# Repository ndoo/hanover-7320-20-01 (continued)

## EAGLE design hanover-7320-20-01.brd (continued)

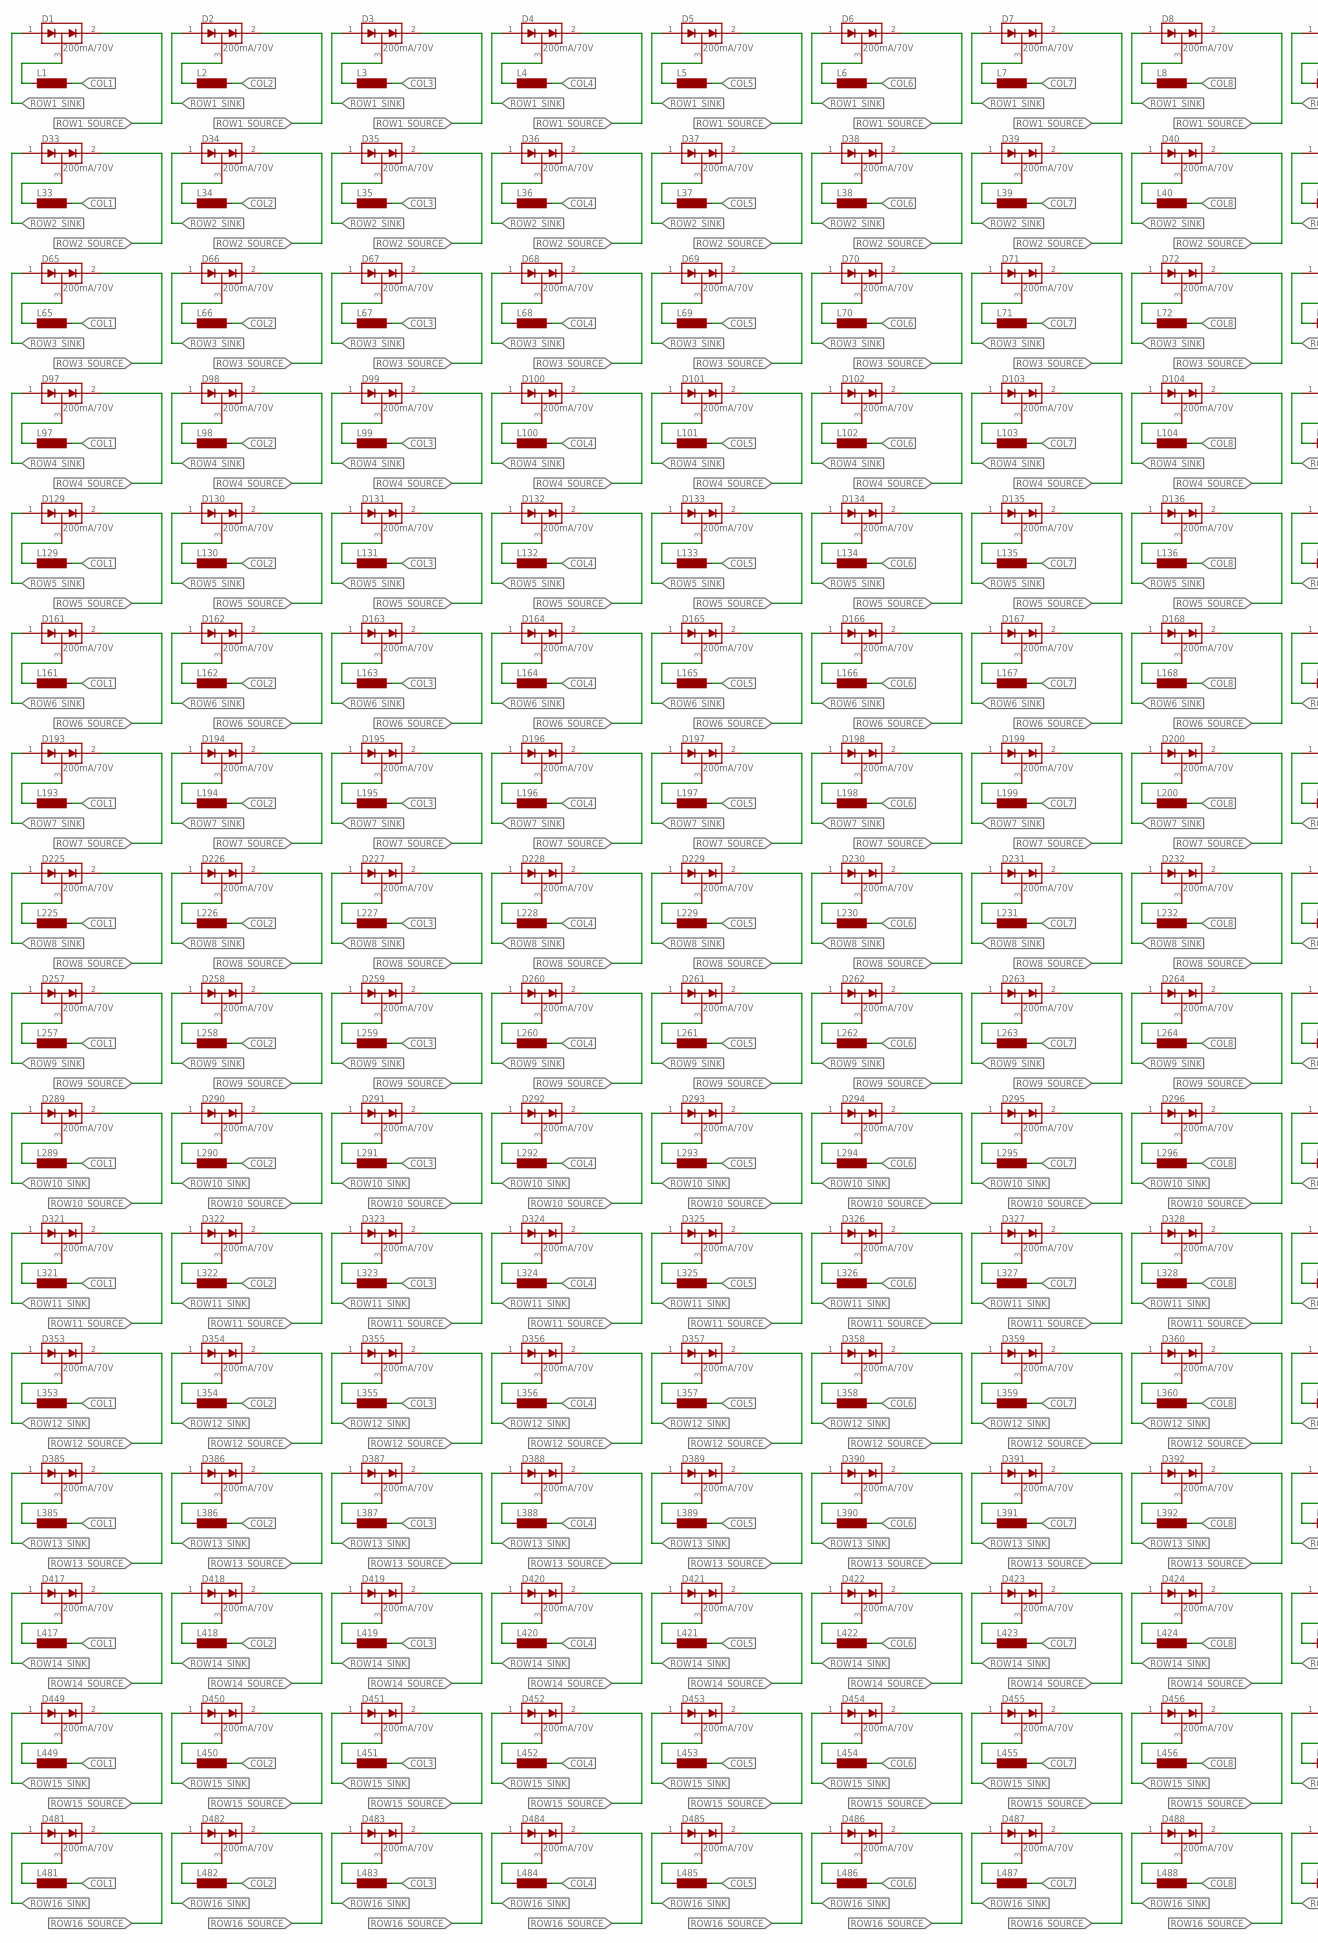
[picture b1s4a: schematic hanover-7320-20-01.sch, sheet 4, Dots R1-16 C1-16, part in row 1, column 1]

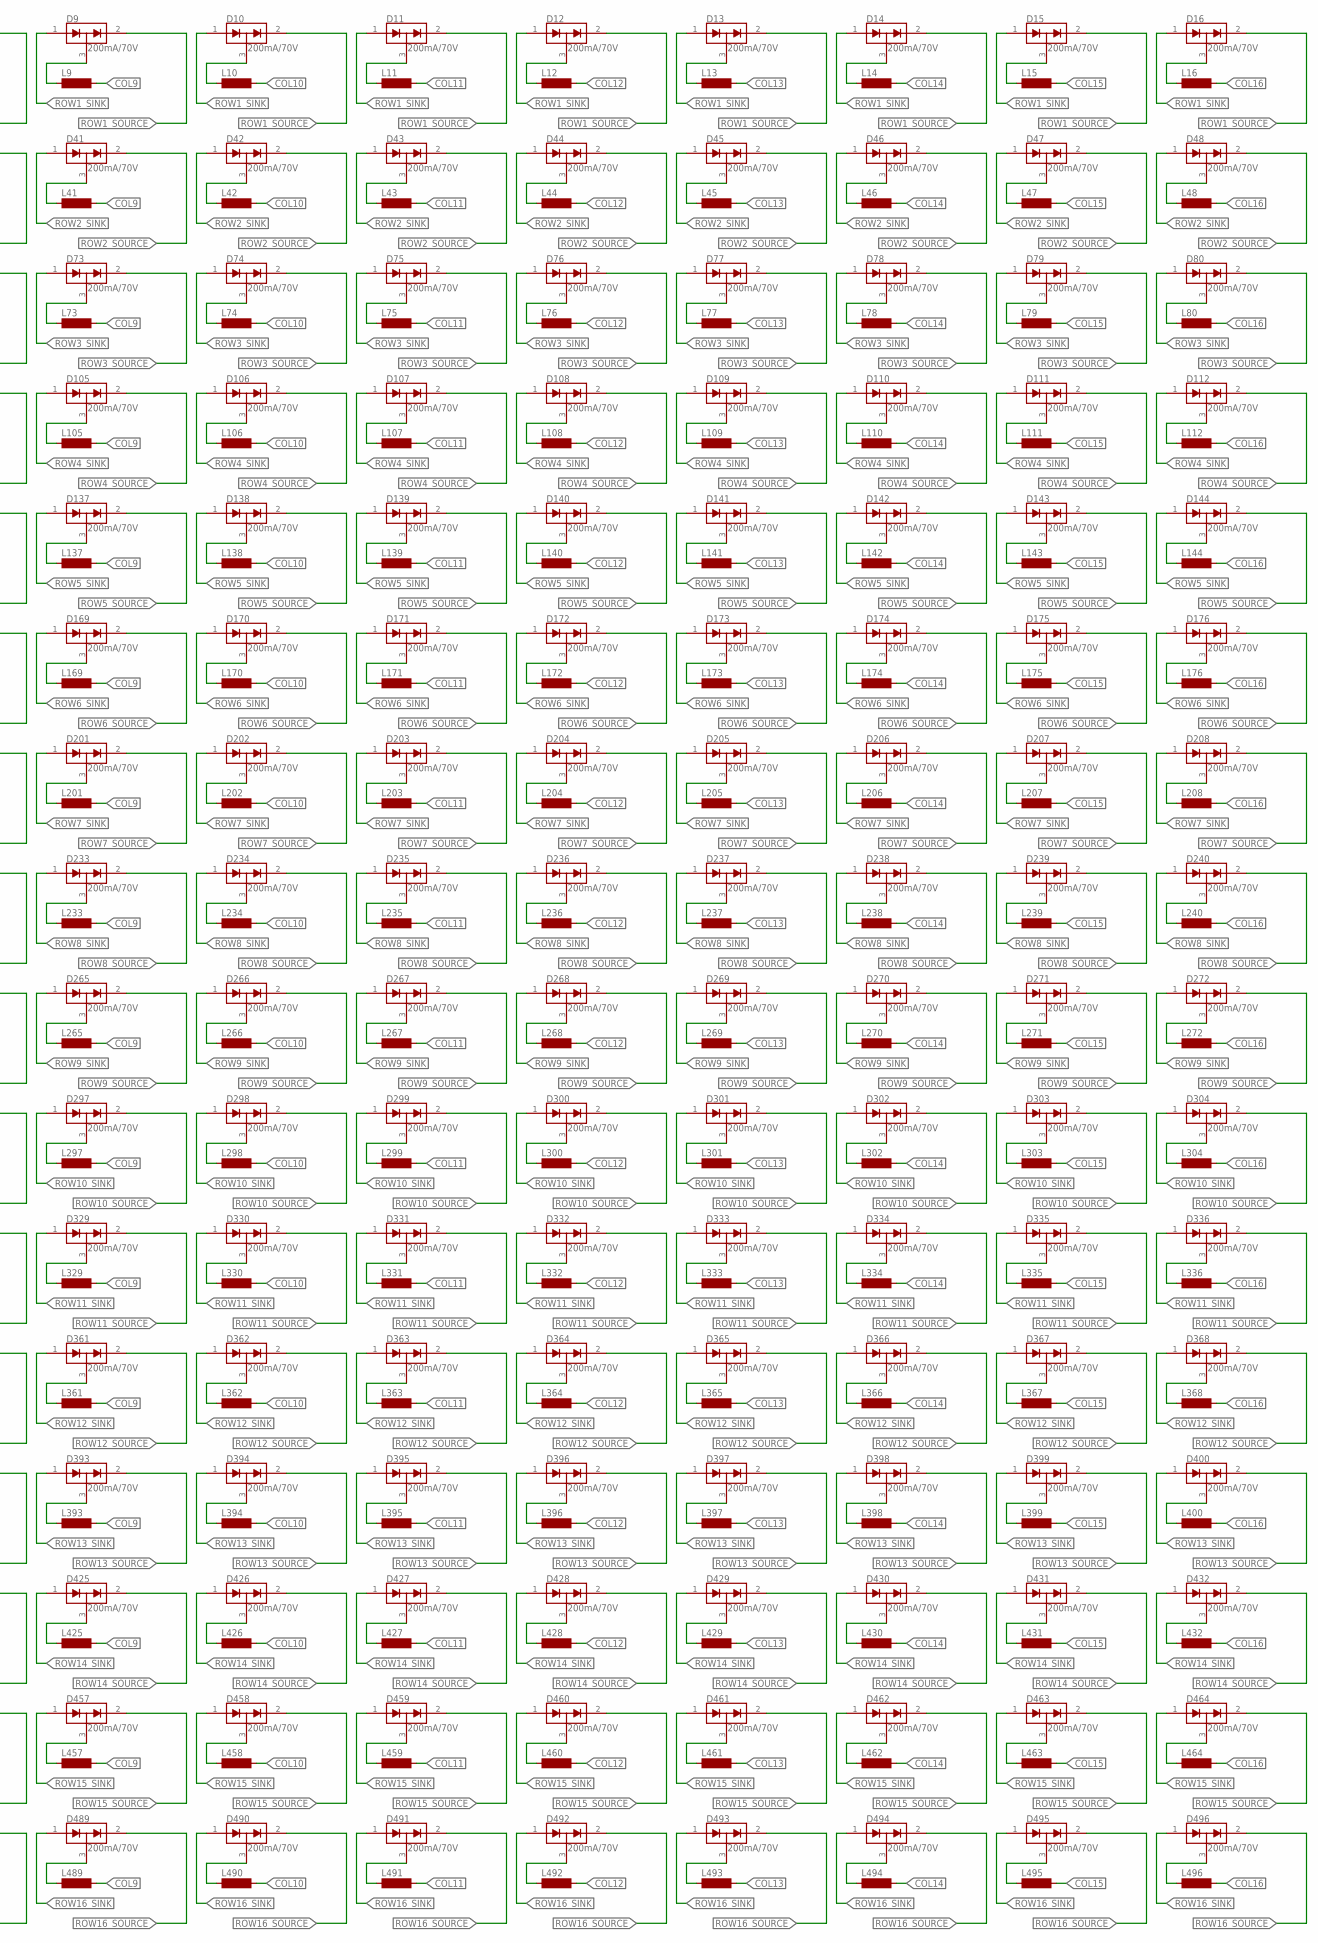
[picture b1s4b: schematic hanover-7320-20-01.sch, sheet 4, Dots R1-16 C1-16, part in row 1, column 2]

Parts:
D1, D2, D3, D4, D5, D6, D7, D8, D9, D10, D11, D12, D13, D14, D15, D16, D33, D34, D35, D36, D37, D38, D39, D40, D41, D42, D43, D44, D45, D46, D47, D48, D65, D66, D67, D68, D69, D70, D71, D72, D73, D74, D75, D76, D77, D78, D79, D80, D97, D98, D99, D100, D101, D102, D103, D104, D105, D106, D107, D108, D109, D110, D111, D112, D129, D130, D131, D132, D133, D134, D135, D136, D137, D138, D139, D140, D141, D142, D143, D144, D161, D162, D163, D164, D165, D166, D167, D168, D169, D170, D171, D172, D173, D174, D175, D176, D193, D194, D195, D196, D197, D198, D199, D200, D201, D202, D203, D204, D205, D206, D207, D208, D225, D226, D227, D228, D229, D230, D231, D232, D233, D234, D235, D236, D237, D238, D239, D240, D257, D258, D259, D260, D261, D262, D263, D264, D265, D266, D267, D268, D269, D270, D271, D272, D289, D290, D291, D292, D293, D294, D295, D296, D297, D298, D299, D300, D301, D302, D303, D304, D321, D322, D323, D324, D325, D326, D327, D328, D329, D330, D331, D332, D333, D334, D335, D336, D353, D354, D355, D356, D357, D358, D359, D360, D361, D362, D363, D364, D365, D366, D367, D368, D385, D386, D387, D388, D389, D390, D391, D392, D393, D394, D395, D396, D397, D398, D399, D400, D417, D418, D419, D420, D421, D422, D423, D424, D425, D426, D427, D428, D429, D430, D431, D432, D449, D450, D451, D452, D453, D454, D455, D456, D457, D458, D459, D460, D461, D462, D463, D464, D481, D482, D483, D484, D485, D486, D487, D488, D489, D490, D491, D492, D493, D494, D495, D496: 200mA/70V; SOT23-3
L1, L2, L3, L4, L5, L6, L7, L8, L9, L10, L11, L12, L13, L14, L15, L16, L33, L34, L35, L36, L37, L38, L39, L40, L41, L42, L43, L44, L45, L46, L47, L48, L65, L66, L67, L68, L69, L70, L71, L72, L73, L74, L75, L76, L77, L78, L79, L80, L97, L98, L99, L100, L101, L102, L103, L104, L105, L106, L107, L108, L109, L110, L111, L112, L129, L130, L131, L132, L133, L134, L135, L136, L137, L138, L139, L140, L141, L142, L143, L144, L161, L162, L163, L164, L165, L166, L167, L168, L169, L170, L171, L172, L173, L174, L175, L176, L193, L194, L195, L196, L197, L198, L199, L200, L201, L202, L203, L204, L205, L206, L207, L208, L225, L226, L227, L228, L229, L230, L231, L232, L233, L234, L235, L236, L237, L238, L239, L240, L257, L258, L259, L260, L261, L262, L263, L264, L265, L266, L267, L268, L269, L270, L271, L272, L289, L290, L291, L292, L293, L294, L295, L296, L297, L298, L299, L300, L301, L302, L303, L304, L321, L322, L323, L324, L325, L326, L327, L328, L329, L330, L331, L332, L333, L334, L335, L336, L353, L354, L355, L356, L357, L358, L359, L360, L361, L362, L363, L364, L365, L366, L367, L368, L385, L386, L387, L388, L389, L390, L391, L392, L393, L394, L395, L396, L397, L398, L399, L400, L417, L418, L419, L420, L421, L422, L423, L424, L425, L426, L427, L428, L429, L430, L431, L432, L449, L450, L451, L452, L453, L454, L455, L456, L457, L458, L459, L460, L461, L462, L463, L464, L481, L482, L483, L484, L485, L486, L487, L488, L489, L490, L491, L492, L493, L494, L495, L496: SD8

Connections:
COL1: L1.2, L33.2, L65.2, L97.2, L129.2, L161.2, L193.2, L225.2, L257.2, L289.2, L321.2, L353.2, L385.2, L417.2, L449.2, L481.2; also elsewhere on the board
COL2: L2.2, L34.2, L66.2, L98.2, L130.2, L162.2, L194.2, L226.2, L258.2, L290.2, L322.2, L354.2, L386.2, L418.2, L450.2, L482.2; also elsewhere on the board
COL3: L3.2, L35.2, L67.2, L99.2, L131.2, L163.2, L195.2, L227.2, L259.2, L291.2, L323.2, L355.2, L387.2, L419.2, L451.2, L483.2; also elsewhere on the board
COL4: L4.2, L36.2, L68.2, L100.2, L132.2, L164.2, L196.2, L228.2, L260.2, L292.2, L324.2, L356.2, L388.2, L420.2, L452.2, L484.2; also elsewhere on the board
COL5: L5.2, L37.2, L69.2, L101.2, L133.2, L165.2, L197.2, L229.2, L261.2, L293.2, L325.2, L357.2, L389.2, L421.2, L453.2, L485.2; also elsewhere on the board
COL6: L6.2, L38.2, L70.2, L102.2, L134.2, L166.2, L198.2, L230.2, L262.2, L294.2, L326.2, L358.2, L390.2, L422.2, L454.2, L486.2; also elsewhere on the board
COL7: L7.2, L39.2, L71.2, L103.2, L135.2, L167.2, L199.2, L231.2, L263.2, L295.2, L327.2, L359.2, L391.2, L423.2, L455.2, L487.2; also elsewhere on the board
COL8: L8.2, L40.2, L72.2, L104.2, L136.2, L168.2, L200.2, L232.2, L264.2, L296.2, L328.2, L360.2, L392.2, L424.2, L456.2, L488.2; also elsewhere on the board
COL9: L9.2, L41.2, L73.2, L105.2, L137.2, L169.2, L201.2, L233.2, L265.2, L297.2, L329.2, L361.2, L393.2, L425.2, L457.2, L489.2; also elsewhere on the board
COL10: L10.2, L42.2, L74.2, L106.2, L138.2, L170.2, L202.2, L234.2, L266.2, L298.2, L330.2, L362.2, L394.2, L426.2, L458.2, L490.2; also elsewhere on the board
COL11: L11.2, L43.2, L75.2, L107.2, L139.2, L171.2, L203.2, L235.2, L267.2, L299.2, L331.2, L363.2, L395.2, L427.2, L459.2, L491.2; also elsewhere on the board
COL12: L12.2, L44.2, L76.2, L108.2, L140.2, L172.2, L204.2, L236.2, L268.2, L300.2, L332.2, L364.2, L396.2, L428.2, L460.2, L492.2; also elsewhere on the board
COL13: L13.2, L45.2, L77.2, L109.2, L141.2, L173.2, L205.2, L237.2, L269.2, L301.2, L333.2, L365.2, L397.2, L429.2, L461.2, L493.2; also elsewhere on the board
COL14: L14.2, L46.2, L78.2, L110.2, L142.2, L174.2, L206.2, L238.2, L270.2, L302.2, L334.2, L366.2, L398.2, L430.2, L462.2, L494.2; also elsewhere on the board
COL15: L15.2, L47.2, L79.2, L111.2, L143.2, L175.2, L207.2, L239.2, L271.2, L303.2, L335.2, L367.2, L399.2, L431.2, L463.2, L495.2; also elsewhere on the board
COL16: L16.2, L48.2, L80.2, L112.2, L144.2, L176.2, L208.2, L240.2, L272.2, L304.2, L336.2, L368.2, L400.2, L432.2, L464.2, L496.2; also elsewhere on the board
unnamed: D1.3 (COM), L1.1
unnamed: D2.3 (COM), L2.1
unnamed: D3.3 (COM), L3.1
unnamed: D4.3 (COM), L4.1
unnamed: D5.3 (COM), L5.1
unnamed: D6.3 (COM), L6.1
unnamed: D7.3 (COM), L7.1
unnamed: D8.3 (COM), L8.1
unnamed: D9.3 (COM), L9.1
unnamed: D10.3 (COM), L10.1
unnamed: D11.3 (COM), L11.1
unnamed: D12.3 (COM), L12.1
unnamed: D13.3 (COM), L13.1
unnamed: D14.3 (COM), L14.1
unnamed: D15.3 (COM), L15.1
unnamed: D16.3 (COM), L16.1
unnamed: D33.3 (COM), L33.1
unnamed: D34.3 (COM), L34.1
unnamed: D35.3 (COM), L35.1
unnamed: D36.3 (COM), L36.1
unnamed: D37.3 (COM), L37.1
unnamed: D38.3 (COM), L38.1
unnamed: D39.3 (COM), L39.1
unnamed: D40.3 (COM), L40.1
unnamed: D41.3 (COM), L41.1
unnamed: D42.3 (COM), L42.1
unnamed: D43.3 (COM), L43.1
unnamed: D44.3 (COM), L44.1
unnamed: D45.3 (COM), L45.1
unnamed: D46.3 (COM), L46.1
unnamed: D47.3 (COM), L47.1
unnamed: D48.3 (COM), L48.1
unnamed: D65.3 (COM), L65.1
unnamed: D66.3 (COM), L66.1
unnamed: D67.3 (COM), L67.1
unnamed: D68.3 (COM), L68.1
unnamed: D69.3 (COM), L69.1
unnamed: D70.3 (COM), L70.1
unnamed: D71.3 (COM), L71.1
unnamed: D72.3 (COM), L72.1
unnamed: D73.3 (COM), L73.1
unnamed: D74.3 (COM), L74.1
unnamed: D75.3 (COM), L75.1
unnamed: D76.3 (COM), L76.1
unnamed: D77.3 (COM), L77.1
unnamed: D78.3 (COM), L78.1
unnamed: D79.3 (COM), L79.1
unnamed: D80.3 (COM), L80.1
unnamed: D97.3 (COM), L97.1
unnamed: D98.3 (COM), L98.1
unnamed: D99.3 (COM), L99.1
unnamed: D100.3 (COM), L100.1
unnamed: D101.3 (COM), L101.1
unnamed: D102.3 (COM), L102.1
unnamed: D103.3 (COM), L103.1
unnamed: D104.3 (COM), L104.1
unnamed: D105.3 (COM), L105.1
unnamed: D106.3 (COM), L106.1
unnamed: D107.3 (COM), L107.1
unnamed: D108.3 (COM), L108.1
unnamed: D109.3 (COM), L109.1
unnamed: D110.3 (COM), L110.1
unnamed: D111.3 (COM), L111.1
unnamed: D112.3 (COM), L112.1
unnamed: D129.3 (COM), L129.1
unnamed: D130.3 (COM), L130.1
unnamed: D131.3 (COM), L131.1
unnamed: D132.3 (COM), L132.1
unnamed: D133.3 (COM), L133.1
unnamed: D134.3 (COM), L134.1
unnamed: D135.3 (COM), L135.1
unnamed: D136.3 (COM), L136.1
unnamed: D137.3 (COM), L137.1
unnamed: D138.3 (COM), L138.1
unnamed: D139.3 (COM), L139.1
unnamed: D140.3 (COM), L140.1
unnamed: D141.3 (COM), L141.1
unnamed: D142.3 (COM), L142.1
unnamed: D143.3 (COM), L143.1
unnamed: D144.3 (COM), L144.1
unnamed: D161.3 (COM), L161.1
unnamed: D162.3 (COM), L162.1
unnamed: D163.3 (COM), L163.1
unnamed: D164.3 (COM), L164.1
unnamed: D165.3 (COM), L165.1
unnamed: D166.3 (COM), L166.1
unnamed: D167.3 (COM), L167.1
unnamed: D168.3 (COM), L168.1
unnamed: D169.3 (COM), L169.1
unnamed: D170.3 (COM), L170.1
unnamed: D171.3 (COM), L171.1
unnamed: D172.3 (COM), L172.1
unnamed: D173.3 (COM), L173.1
unnamed: D174.3 (COM), L174.1
unnamed: D175.3 (COM), L175.1
unnamed: D176.3 (COM), L176.1
unnamed: D193.3 (COM), L193.1
unnamed: D194.3 (COM), L194.1
unnamed: D195.3 (COM), L195.1
unnamed: D196.3 (COM), L196.1
unnamed: D197.3 (COM), L197.1
unnamed: D198.3 (COM), L198.1
unnamed: D199.3 (COM), L199.1
unnamed: D200.3 (COM), L200.1
unnamed: D201.3 (COM), L201.1
unnamed: D202.3 (COM), L202.1
unnamed: D203.3 (COM), L203.1
unnamed: D204.3 (COM), L204.1
unnamed: D205.3 (COM), L205.1
unnamed: D206.3 (COM), L206.1
unnamed: D207.3 (COM), L207.1
unnamed: D208.3 (COM), L208.1
unnamed: D225.3 (COM), L225.1
unnamed: D226.3 (COM), L226.1
unnamed: D227.3 (COM), L227.1
unnamed: D228.3 (COM), L228.1
unnamed: D229.3 (COM), L229.1
unnamed: D230.3 (COM), L230.1
unnamed: D231.3 (COM), L231.1
unnamed: D232.3 (COM), L232.1
unnamed: D233.3 (COM), L233.1
unnamed: D234.3 (COM), L234.1
unnamed: D235.3 (COM), L235.1
unnamed: D236.3 (COM), L236.1
unnamed: D237.3 (COM), L237.1
unnamed: D238.3 (COM), L238.1
unnamed: D239.3 (COM), L239.1
unnamed: D240.3 (COM), L240.1
unnamed: D257.3 (COM), L257.1
unnamed: D258.3 (COM), L258.1
unnamed: D259.3 (COM), L259.1
unnamed: D260.3 (COM), L260.1
unnamed: D261.3 (COM), L261.1
unnamed: D262.3 (COM), L262.1
unnamed: D263.3 (COM), L263.1
unnamed: D264.3 (COM), L264.1
unnamed: D265.3 (COM), L265.1
unnamed: D266.3 (COM), L266.1
unnamed: D267.3 (COM), L267.1
unnamed: D268.3 (COM), L268.1
unnamed: D269.3 (COM), L269.1
unnamed: D270.3 (COM), L270.1
unnamed: D271.3 (COM), L271.1
unnamed: D272.3 (COM), L272.1
unnamed: D289.3 (COM), L289.1
unnamed: D290.3 (COM), L290.1
unnamed: D291.3 (COM), L291.1
unnamed: D292.3 (COM), L292.1
unnamed: D293.3 (COM), L293.1
unnamed: D294.3 (COM), L294.1
unnamed: D295.3 (COM), L295.1
unnamed: D296.3 (COM), L296.1
unnamed: D297.3 (COM), L297.1
unnamed: D298.3 (COM), L298.1
unnamed: D299.3 (COM), L299.1
unnamed: D300.3 (COM), L300.1
unnamed: D301.3 (COM), L301.1
unnamed: D302.3 (COM), L302.1
unnamed: D303.3 (COM), L303.1
unnamed: D304.3 (COM), L304.1
unnamed: D321.3 (COM), L321.1
unnamed: D322.3 (COM), L322.1
unnamed: D323.3 (COM), L323.1
unnamed: D324.3 (COM), L324.1
unnamed: D325.3 (COM), L325.1
unnamed: D326.3 (COM), L326.1
unnamed: D327.3 (COM), L327.1
unnamed: D328.3 (COM), L328.1
unnamed: D329.3 (COM), L329.1
unnamed: D330.3 (COM), L330.1
unnamed: D331.3 (COM), L331.1
unnamed: D332.3 (COM), L332.1
unnamed: D333.3 (COM), L333.1
unnamed: D334.3 (COM), L334.1
unnamed: D335.3 (COM), L335.1
unnamed: D336.3 (COM), L336.1
unnamed: D353.3 (COM), L353.1
unnamed: D354.3 (COM), L354.1
unnamed: D355.3 (COM), L355.1
unnamed: D356.3 (COM), L356.1
unnamed: D357.3 (COM), L357.1
unnamed: D358.3 (COM), L358.1
unnamed: D359.3 (COM), L359.1
unnamed: D360.3 (COM), L360.1
unnamed: D361.3 (COM), L361.1
unnamed: D362.3 (COM), L362.1
unnamed: D363.3 (COM), L363.1
unnamed: D364.3 (COM), L364.1
unnamed: D365.3 (COM), L365.1
unnamed: D366.3 (COM), L366.1
unnamed: D367.3 (COM), L367.1
unnamed: D368.3 (COM), L368.1
unnamed: D385.3 (COM), L385.1
unnamed: D386.3 (COM), L386.1
unnamed: D387.3 (COM), L387.1
unnamed: D388.3 (COM), L388.1
unnamed: D389.3 (COM), L389.1
unnamed: D390.3 (COM), L390.1
unnamed: D391.3 (COM), L391.1
unnamed: D392.3 (COM), L392.1
unnamed: D393.3 (COM), L393.1
unnamed: D394.3 (COM), L394.1
unnamed: D395.3 (COM), L395.1
unnamed: D396.3 (COM), L396.1
unnamed: D397.3 (COM), L397.1
unnamed: D398.3 (COM), L398.1
unnamed: D399.3 (COM), L399.1
unnamed: D400.3 (COM), L400.1
unnamed: D417.3 (COM), L417.1
unnamed: D418.3 (COM), L418.1
unnamed: D419.3 (COM), L419.1
unnamed: D420.3 (COM), L420.1
unnamed: D421.3 (COM), L421.1
unnamed: D422.3 (COM), L422.1
unnamed: D423.3 (COM), L423.1
unnamed: D424.3 (COM), L424.1
unnamed: D425.3 (COM), L425.1
unnamed: D426.3 (COM), L426.1
unnamed: D427.3 (COM), L427.1
unnamed: D428.3 (COM), L428.1
unnamed: D429.3 (COM), L429.1
unnamed: D430.3 (COM), L430.1
unnamed: D431.3 (COM), L431.1
unnamed: D432.3 (COM), L432.1
unnamed: D449.3 (COM), L449.1
unnamed: D450.3 (COM), L450.1
unnamed: D451.3 (COM), L451.1
unnamed: D452.3 (COM), L452.1
unnamed: D453.3 (COM), L453.1
unnamed: D454.3 (COM), L454.1
unnamed: D455.3 (COM), L455.1
unnamed: D456.3 (COM), L456.1
unnamed: D457.3 (COM), L457.1
unnamed: D458.3 (COM), L458.1
unnamed: D459.3 (COM), L459.1
unnamed: D460.3 (COM), L460.1
unnamed: D461.3 (COM), L461.1
unnamed: D462.3 (COM), L462.1
unnamed: D463.3 (COM), L463.1
unnamed: D464.3 (COM), L464.1
unnamed: D481.3 (COM), L481.1
unnamed: D482.3 (COM), L482.1
unnamed: D483.3 (COM), L483.1
unnamed: D484.3 (COM), L484.1
unnamed: D485.3 (COM), L485.1
unnamed: D486.3 (COM), L486.1
unnamed: D487.3 (COM), L487.1
unnamed: D488.3 (COM), L488.1
unnamed: D489.3 (COM), L489.1
unnamed: D490.3 (COM), L490.1
unnamed: D491.3 (COM), L491.1
unnamed: D492.3 (COM), L492.1
unnamed: D493.3 (COM), L493.1
unnamed: D494.3 (COM), L494.1
unnamed: D495.3 (COM), L495.1
unnamed: D496.3 (COM), L496.1
ROW1_SINK: D1.1 (A1), D2.1 (A1), D3.1 (A1), D4.1 (A1), D5.1 (A1), D6.1 (A1), D7.1 (A1), D8.1 (A1), D9.1 (A1), D10.1 (A1), D11.1 (A1), D12.1 (A1), D13.1 (A1), D14.1 (A1), D15.1 (A1), D16.1 (A1); also elsewhere on the board
ROW1_SOURCE: D1.2 (C2), D2.2 (C2), D3.2 (C2), D4.2 (C2), D5.2 (C2), D6.2 (C2), D7.2 (C2), D8.2 (C2), D9.2 (C2), D10.2 (C2), D11.2 (C2), D12.2 (C2), D13.2 (C2), D14.2 (C2), D15.2 (C2), D16.2 (C2); also elsewhere on the board
ROW2_SINK: D33.1 (A1), D34.1 (A1), D35.1 (A1), D36.1 (A1), D37.1 (A1), D38.1 (A1), D39.1 (A1), D40.1 (A1), D41.1 (A1), D42.1 (A1), D43.1 (A1), D44.1 (A1), D45.1 (A1), D46.1 (A1), D47.1 (A1), D48.1 (A1); also elsewhere on the board
ROW2_SOURCE: D33.2 (C2), D34.2 (C2), D35.2 (C2), D36.2 (C2), D37.2 (C2), D38.2 (C2), D39.2 (C2), D40.2 (C2), D41.2 (C2), D42.2 (C2), D43.2 (C2), D44.2 (C2), D45.2 (C2), D46.2 (C2), D47.2 (C2), D48.2 (C2); also elsewhere on the board
ROW3_SINK: D65.1 (A1), D66.1 (A1), D67.1 (A1), D68.1 (A1), D69.1 (A1), D70.1 (A1), D71.1 (A1), D72.1 (A1), D73.1 (A1), D74.1 (A1), D75.1 (A1), D76.1 (A1), D77.1 (A1), D78.1 (A1), D79.1 (A1), D80.1 (A1); also elsewhere on the board
ROW3_SOURCE: D65.2 (C2), D66.2 (C2), D67.2 (C2), D68.2 (C2), D69.2 (C2), D70.2 (C2), D71.2 (C2), D72.2 (C2), D73.2 (C2), D74.2 (C2), D75.2 (C2), D76.2 (C2), D77.2 (C2), D78.2 (C2), D79.2 (C2), D80.2 (C2); also elsewhere on the board
ROW4_SINK: D97.1 (A1), D98.1 (A1), D99.1 (A1), D100.1 (A1), D101.1 (A1), D102.1 (A1), D103.1 (A1), D104.1 (A1), D105.1 (A1), D106.1 (A1), D107.1 (A1), D108.1 (A1), D109.1 (A1), D110.1 (A1), D111.1 (A1), D112.1 (A1); also elsewhere on the board
ROW4_SOURCE: D97.2 (C2), D98.2 (C2), D99.2 (C2), D100.2 (C2), D101.2 (C2), D102.2 (C2), D103.2 (C2), D104.2 (C2), D105.2 (C2), D106.2 (C2), D107.2 (C2), D108.2 (C2), D109.2 (C2), D110.2 (C2), D111.2 (C2), D112.2 (C2); also elsewhere on the board
ROW5_SINK: D129.1 (A1), D130.1 (A1), D131.1 (A1), D132.1 (A1), D133.1 (A1), D134.1 (A1), D135.1 (A1), D136.1 (A1), D137.1 (A1), D138.1 (A1), D139.1 (A1), D140.1 (A1), D141.1 (A1), D142.1 (A1), D143.1 (A1), D144.1 (A1); also elsewhere on the board
ROW5_SOURCE: D129.2 (C2), D130.2 (C2), D131.2 (C2), D132.2 (C2), D133.2 (C2), D134.2 (C2), D135.2 (C2), D136.2 (C2), D137.2 (C2), D138.2 (C2), D139.2 (C2), D140.2 (C2), D141.2 (C2), D142.2 (C2), D143.2 (C2), D144.2 (C2); also elsewhere on the board
ROW6_SINK: D161.1 (A1), D162.1 (A1), D163.1 (A1), D164.1 (A1), D165.1 (A1), D166.1 (A1), D167.1 (A1), D168.1 (A1), D169.1 (A1), D170.1 (A1), D171.1 (A1), D172.1 (A1), D173.1 (A1), D174.1 (A1), D175.1 (A1), D176.1 (A1); also elsewhere on the board
ROW6_SOURCE: D161.2 (C2), D162.2 (C2), D163.2 (C2), D164.2 (C2), D165.2 (C2), D166.2 (C2), D167.2 (C2), D168.2 (C2), D169.2 (C2), D170.2 (C2), D171.2 (C2), D172.2 (C2), D173.2 (C2), D174.2 (C2), D175.2 (C2), D176.2 (C2); also elsewhere on the board
ROW7_SINK: D193.1 (A1), D194.1 (A1), D195.1 (A1), D196.1 (A1), D197.1 (A1), D198.1 (A1), D199.1 (A1), D200.1 (A1), D201.1 (A1), D202.1 (A1), D203.1 (A1), D204.1 (A1), D205.1 (A1), D206.1 (A1), D207.1 (A1), D208.1 (A1); also elsewhere on the board
ROW7_SOURCE: D193.2 (C2), D194.2 (C2), D195.2 (C2), D196.2 (C2), D197.2 (C2), D198.2 (C2), D199.2 (C2), D200.2 (C2), D201.2 (C2), D202.2 (C2), D203.2 (C2), D204.2 (C2), D205.2 (C2), D206.2 (C2), D207.2 (C2), D208.2 (C2); also elsewhere on the board
ROW8_SINK: D225.1 (A1), D226.1 (A1), D227.1 (A1), D228.1 (A1), D229.1 (A1), D230.1 (A1), D231.1 (A1), D232.1 (A1), D233.1 (A1), D234.1 (A1), D235.1 (A1), D236.1 (A1), D237.1 (A1), D238.1 (A1), D239.1 (A1), D240.1 (A1); also elsewhere on the board
ROW8_SOURCE: D225.2 (C2), D226.2 (C2), D227.2 (C2), D228.2 (C2), D229.2 (C2), D230.2 (C2), D231.2 (C2), D232.2 (C2), D233.2 (C2), D234.2 (C2), D235.2 (C2), D236.2 (C2), D237.2 (C2), D238.2 (C2), D239.2 (C2), D240.2 (C2); also elsewhere on the board
ROW9_SINK: D257.1 (A1), D258.1 (A1), D259.1 (A1), D260.1 (A1), D261.1 (A1), D262.1 (A1), D263.1 (A1), D264.1 (A1), D265.1 (A1), D266.1 (A1), D267.1 (A1), D268.1 (A1), D269.1 (A1), D270.1 (A1), D271.1 (A1), D272.1 (A1); also elsewhere on the board
ROW9_SOURCE: D257.2 (C2), D258.2 (C2), D259.2 (C2), D260.2 (C2), D261.2 (C2), D262.2 (C2), D263.2 (C2), D264.2 (C2), D265.2 (C2), D266.2 (C2), D267.2 (C2), D268.2 (C2), D269.2 (C2), D270.2 (C2), D271.2 (C2), D272.2 (C2); also elsewhere on the board
ROW10_SINK: D289.1 (A1), D290.1 (A1), D291.1 (A1), D292.1 (A1), D293.1 (A1), D294.1 (A1), D295.1 (A1), D296.1 (A1), D297.1 (A1), D298.1 (A1), D299.1 (A1), D300.1 (A1), D301.1 (A1), D302.1 (A1), D303.1 (A1), D304.1 (A1); also elsewhere on the board
ROW10_SOURCE: D289.2 (C2), D290.2 (C2), D291.2 (C2), D292.2 (C2), D293.2 (C2), D294.2 (C2), D295.2 (C2), D296.2 (C2), D297.2 (C2), D298.2 (C2), D299.2 (C2), D300.2 (C2), D301.2 (C2), D302.2 (C2), D303.2 (C2), D304.2 (C2); also elsewhere on the board
ROW11_SINK: D321.1 (A1), D322.1 (A1), D323.1 (A1), D324.1 (A1), D325.1 (A1), D326.1 (A1), D327.1 (A1), D328.1 (A1), D329.1 (A1), D330.1 (A1), D331.1 (A1), D332.1 (A1), D333.1 (A1), D334.1 (A1), D335.1 (A1), D336.1 (A1); also elsewhere on the board
ROW11_SOURCE: D321.2 (C2), D322.2 (C2), D323.2 (C2), D324.2 (C2), D325.2 (C2), D326.2 (C2), D327.2 (C2), D328.2 (C2), D329.2 (C2), D330.2 (C2), D331.2 (C2), D332.2 (C2), D333.2 (C2), D334.2 (C2), D335.2 (C2), D336.2 (C2); also elsewhere on the board
ROW12_SINK: D353.1 (A1), D354.1 (A1), D355.1 (A1), D356.1 (A1), D357.1 (A1), D358.1 (A1), D359.1 (A1), D360.1 (A1), D361.1 (A1), D362.1 (A1), D363.1 (A1), D364.1 (A1), D365.1 (A1), D366.1 (A1), D367.1 (A1), D368.1 (A1); also elsewhere on the board
ROW12_SOURCE: D353.2 (C2), D354.2 (C2), D355.2 (C2), D356.2 (C2), D357.2 (C2), D358.2 (C2), D359.2 (C2), D360.2 (C2), D361.2 (C2), D362.2 (C2), D363.2 (C2), D364.2 (C2), D365.2 (C2), D366.2 (C2), D367.2 (C2), D368.2 (C2); also elsewhere on the board
ROW13_SINK: D385.1 (A1), D386.1 (A1), D387.1 (A1), D388.1 (A1), D389.1 (A1), D390.1 (A1), D391.1 (A1), D392.1 (A1), D393.1 (A1), D394.1 (A1), D395.1 (A1), D396.1 (A1), D397.1 (A1), D398.1 (A1), D399.1 (A1), D400.1 (A1); also elsewhere on the board
ROW13_SOURCE: D385.2 (C2), D386.2 (C2), D387.2 (C2), D388.2 (C2), D389.2 (C2), D390.2 (C2), D391.2 (C2), D392.2 (C2), D393.2 (C2), D394.2 (C2), D395.2 (C2), D396.2 (C2), D397.2 (C2), D398.2 (C2), D399.2 (C2), D400.2 (C2); also elsewhere on the board
ROW14_SINK: D417.1 (A1), D418.1 (A1), D419.1 (A1), D420.1 (A1), D421.1 (A1), D422.1 (A1), D423.1 (A1), D424.1 (A1), D425.1 (A1), D426.1 (A1), D427.1 (A1), D428.1 (A1), D429.1 (A1), D430.1 (A1), D431.1 (A1), D432.1 (A1); also elsewhere on the board
ROW14_SOURCE: D417.2 (C2), D418.2 (C2), D419.2 (C2), D420.2 (C2), D421.2 (C2), D422.2 (C2), D423.2 (C2), D424.2 (C2), D425.2 (C2), D426.2 (C2), D427.2 (C2), D428.2 (C2), D429.2 (C2), D430.2 (C2), D431.2 (C2), D432.2 (C2); also elsewhere on the board
ROW15_SINK: D449.1 (A1), D450.1 (A1), D451.1 (A1), D452.1 (A1), D453.1 (A1), D454.1 (A1), D455.1 (A1), D456.1 (A1), D457.1 (A1), D458.1 (A1), D459.1 (A1), D460.1 (A1), D461.1 (A1), D462.1 (A1), D463.1 (A1), D464.1 (A1); also elsewhere on the board
ROW15_SOURCE: D449.2 (C2), D450.2 (C2), D451.2 (C2), D452.2 (C2), D453.2 (C2), D454.2 (C2), D455.2 (C2), D456.2 (C2), D457.2 (C2), D458.2 (C2), D459.2 (C2), D460.2 (C2), D461.2 (C2), D462.2 (C2), D463.2 (C2), D464.2 (C2); also elsewhere on the board
ROW16_SINK: D481.1 (A1), D482.1 (A1), D483.1 (A1), D484.1 (A1), D485.1 (A1), D486.1 (A1), D487.1 (A1), D488.1 (A1), D489.1 (A1), D490.1 (A1), D491.1 (A1), D492.1 (A1), D493.1 (A1), D494.1 (A1), D495.1 (A1), D496.1 (A1); also elsewhere on the board
ROW16_SOURCE: D481.2 (C2), D482.2 (C2), D483.2 (C2), D484.2 (C2), D485.2 (C2), D486.2 (C2), D487.2 (C2), D488.2 (C2), D489.2 (C2), D490.2 (C2), D491.2 (C2), D492.2 (C2), D493.2 (C2), D494.2 (C2), D495.2 (C2), D496.2 (C2); also elsewhere on the board
